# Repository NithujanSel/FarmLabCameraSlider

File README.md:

# Camera slider

### Student 1: Nithujan Selvaratnam

### Student 2: Jesse Denaux

### Student 3: Tarun Singh

<a href="https://nithujansel.github.io/FarmLabCameraSlider/">Docsify Page</a><br>

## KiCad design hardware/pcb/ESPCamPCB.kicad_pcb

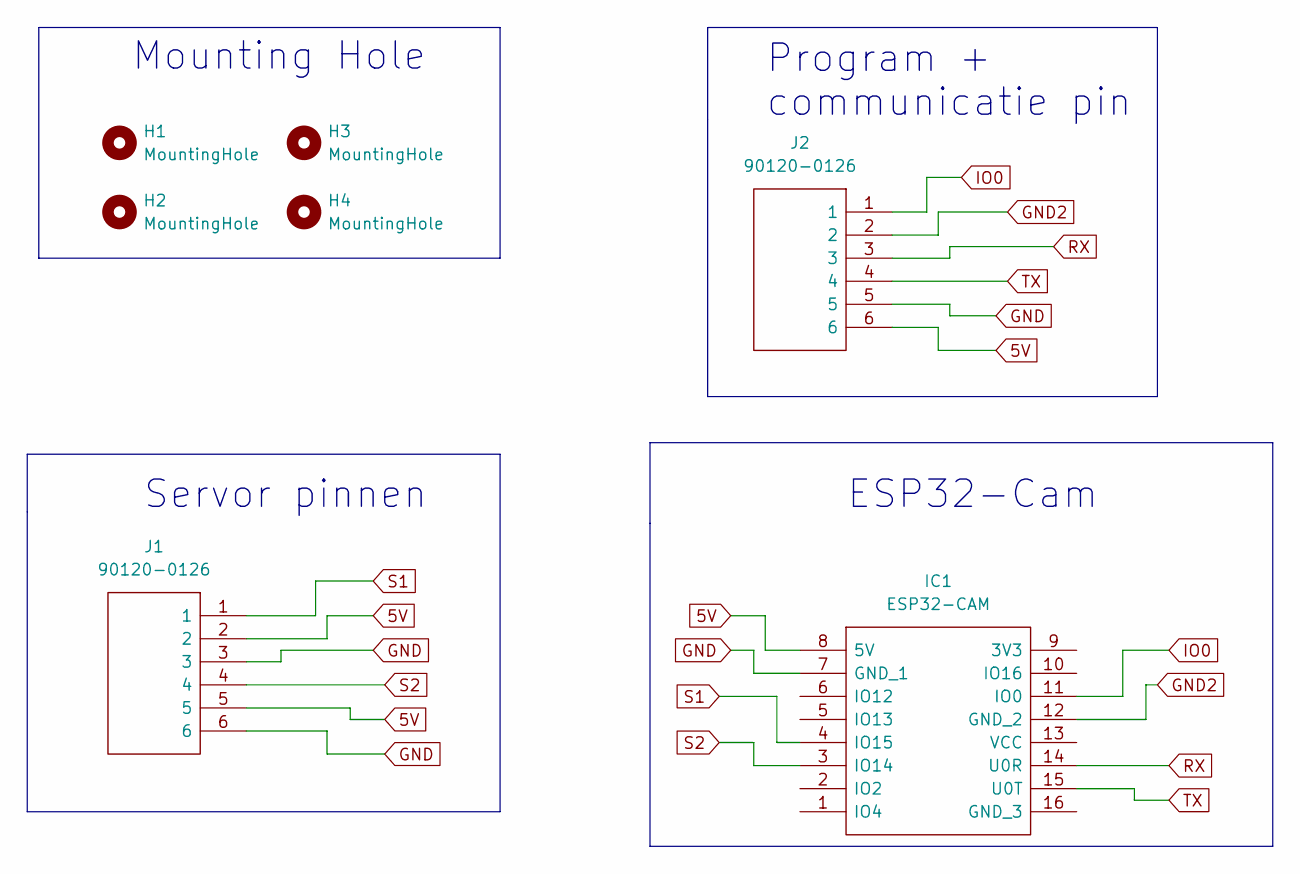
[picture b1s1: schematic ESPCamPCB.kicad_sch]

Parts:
H1, H2, H3, H4: MountingHole; MountingHole_2.7mm
IC1: ESP32-CAM; ESP32CAM; Manufacturer_Part_Number ESP32-CAM
J1, J2: 90120-0126; HDRV6W65P0X254_1X6_1502X249X560P; Manufacturer_Part_Number 90120-0126; Mouser Part Number 538-90120-0126

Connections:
5V: IC1.8 (5V), J1.2, J1.5, J2.6
GND: IC1.7 (GND_1), J1.3, J1.6, J2.5
GND2: IC1.12 (GND_2), J2.2
IO0: IC1.11 (IO0), J2.1
RX: IC1.14 (U0R), J2.3
S1: IC1.4 (IO15), J1.1
S2: IC1.3 (IO14), J1.4
TX: IC1.15 (U0T), J2.4

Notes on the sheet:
ESP32-Cam
Program + communicatie pin
Mounting Hole
Servor pinnen

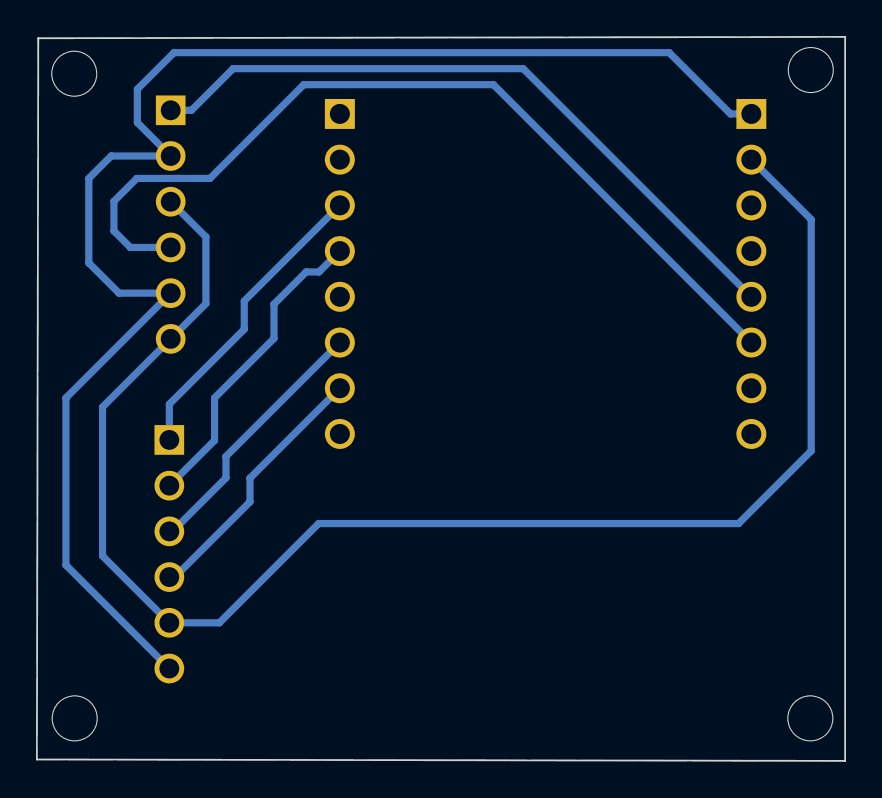
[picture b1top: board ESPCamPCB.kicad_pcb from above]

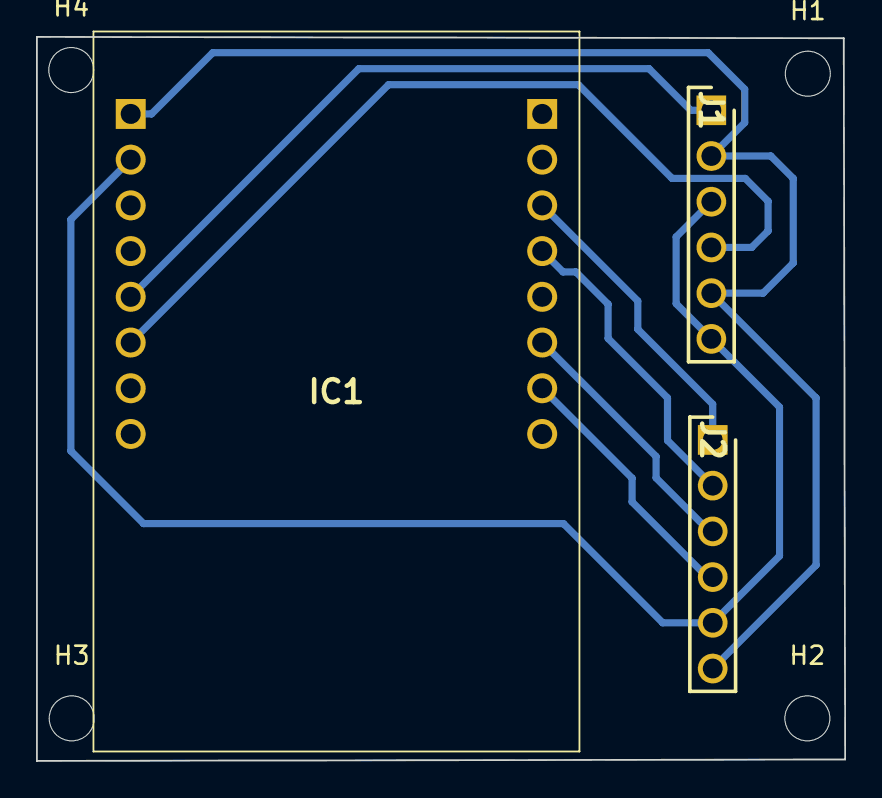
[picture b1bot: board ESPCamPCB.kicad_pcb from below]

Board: 2 copper layers, 44.9 x 40.2 mm, 7 parts (7 on the bottom side), 8 nets.

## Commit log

2022-10-28 testV1
2022-10-28 Structuur
2022-10-28 V1.5
2022-10-28 V1.6
2022-10-28 V1.7
2022-10-28 error fix
2022-10-28 errorFix
2022-10-28 URL fix
2022-10-28 imgSizeFix
2022-10-28 3Dmodel error
